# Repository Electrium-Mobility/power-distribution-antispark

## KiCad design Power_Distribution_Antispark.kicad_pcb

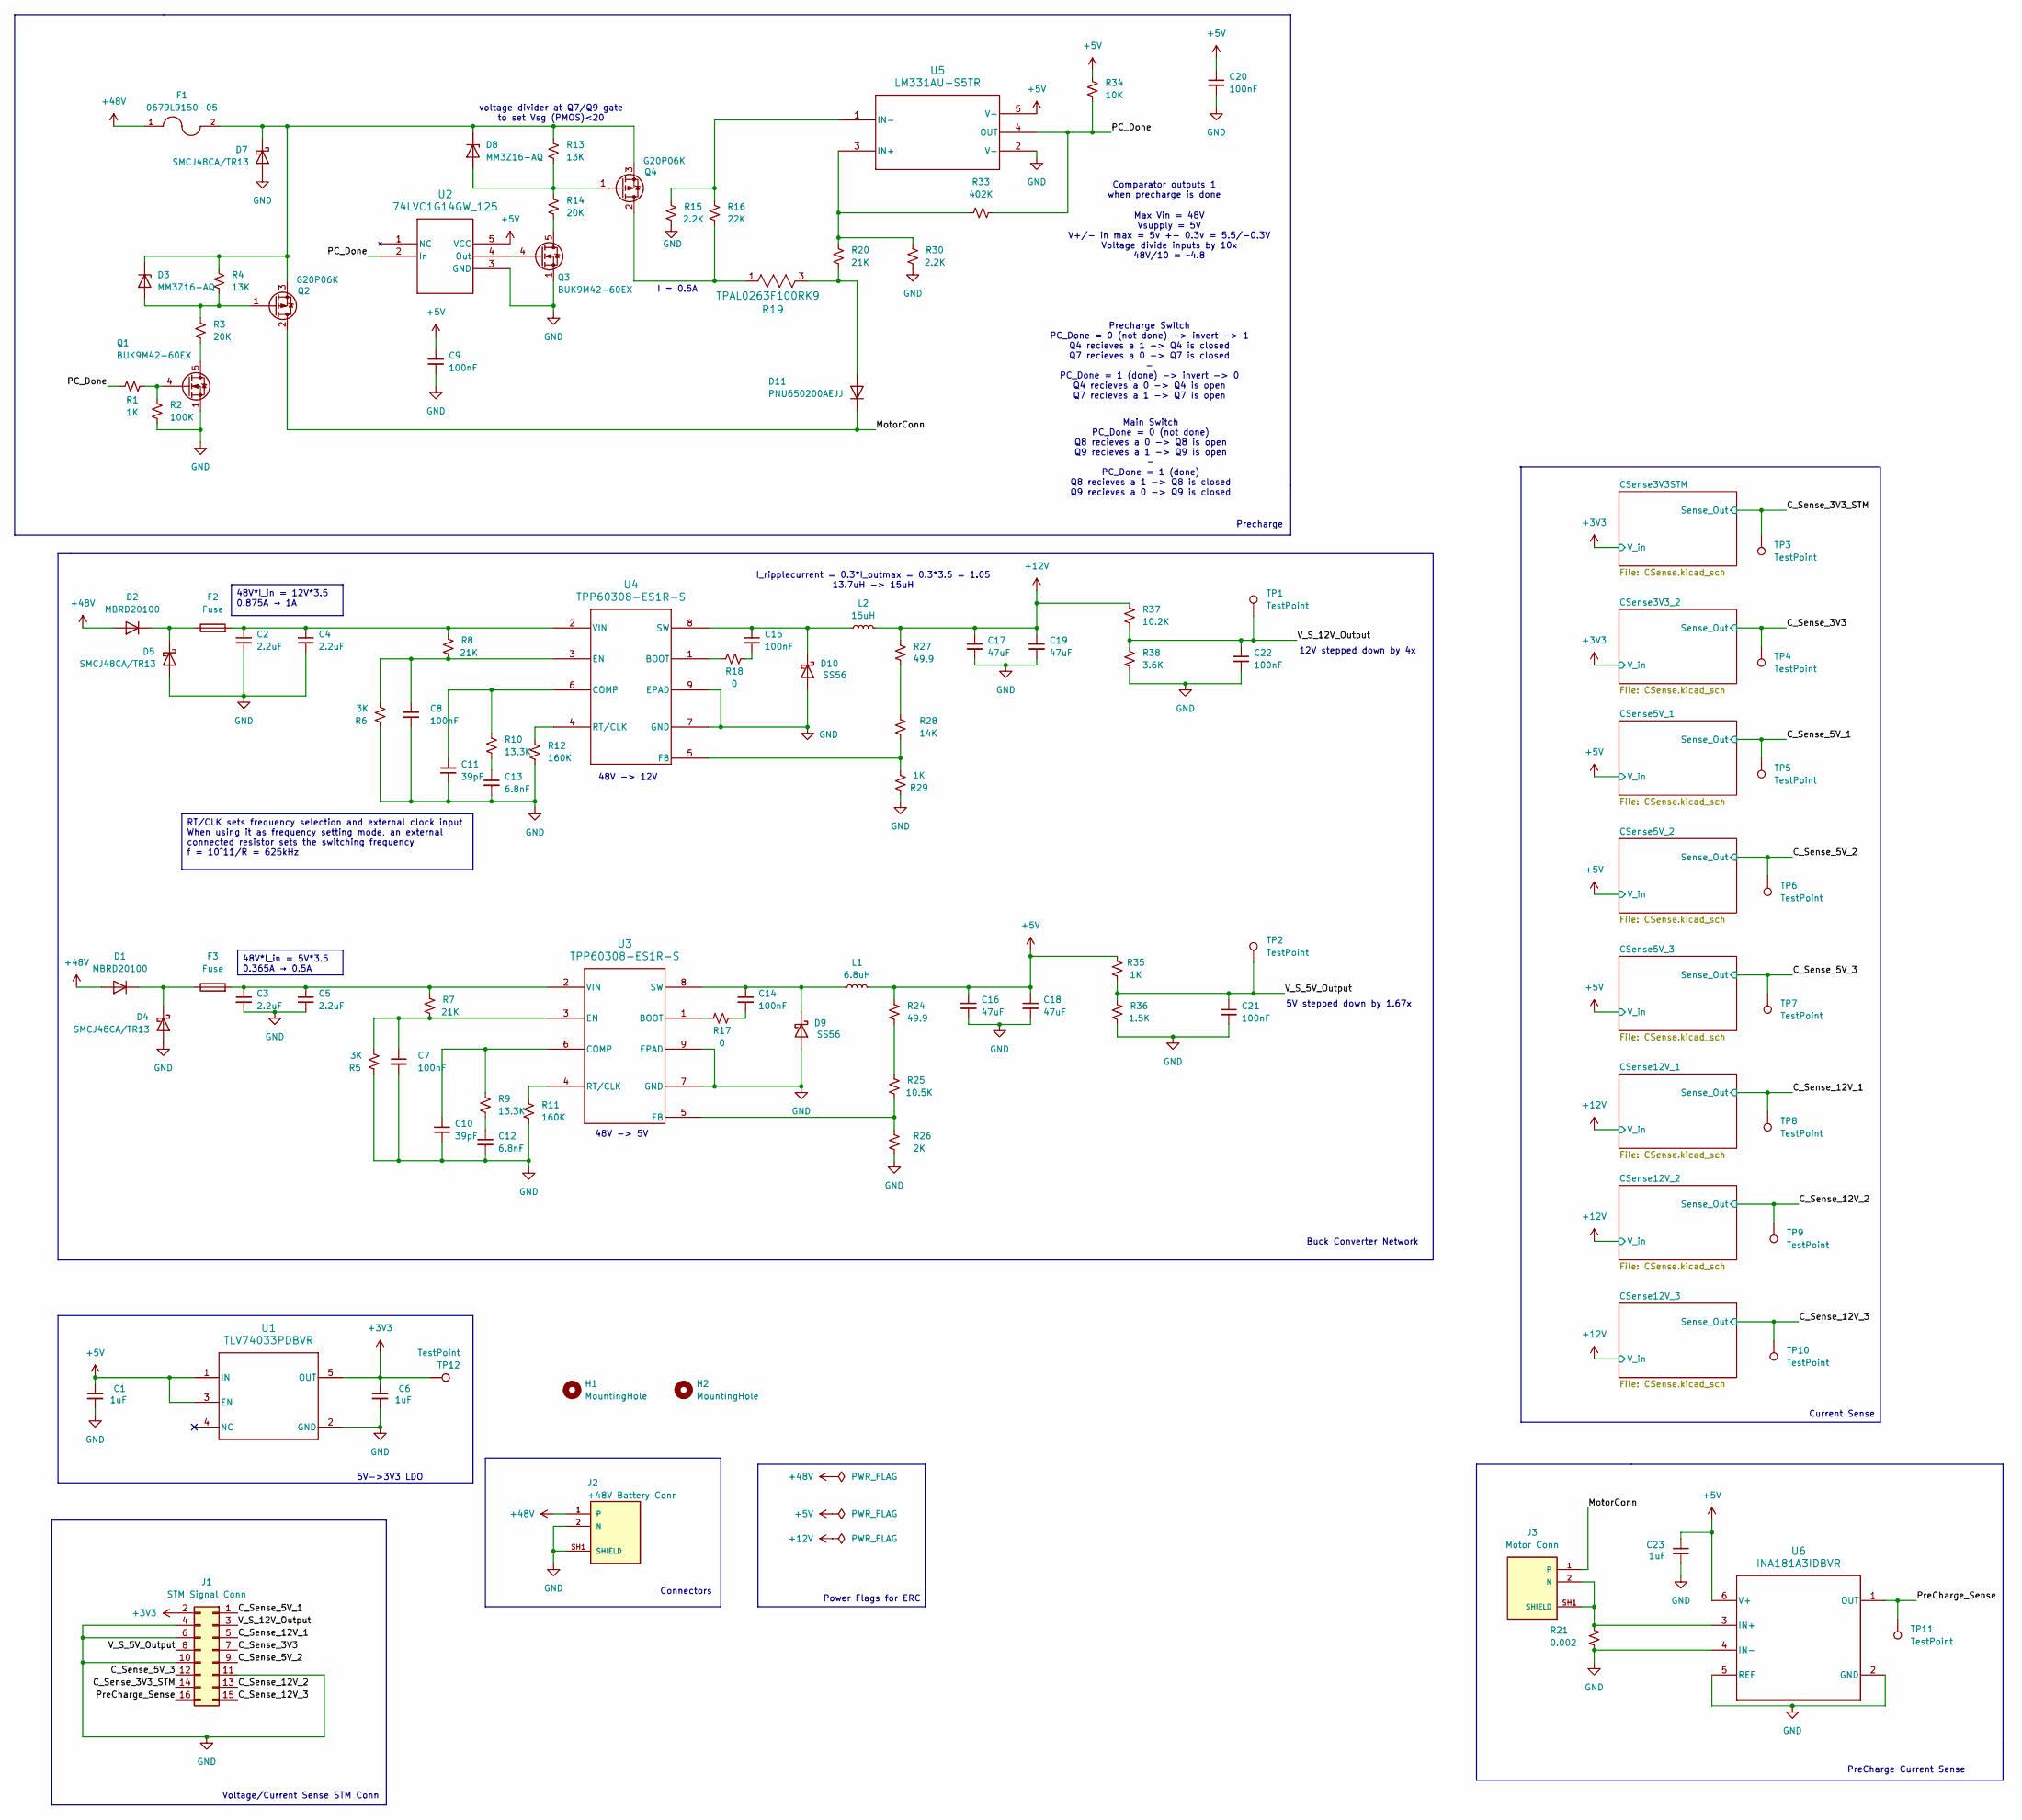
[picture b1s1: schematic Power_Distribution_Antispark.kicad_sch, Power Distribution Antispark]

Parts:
C1, C6, C23: 1uF; C_0603_1608Metric
C2, C3, C4, C5: 2.2uF; C_1206_3216Metric
C7, C8, C9, C14, C15, C20, C21, C22: 100nF; C_0603_1608Metric
C10, C11: 39pF; C_0603_1608Metric
C12, C13: 6.8nF; C_0603_1608Metric
C16, C17, C18, C19: 47uF; C_1206_3216Metric
D1, D2: MBRD20100; TO-252-3_TabPin2
D3, D8: MM3Z16-AQ; D_SOD-323F
D4, D5, D7: SMCJ48CA/TR13; D_SMC
D9, D10: SS56; D_SMA
D11: PNU650200AEJJ; TO-263-3_TabPin2
F1: 0679L9150-05; FUSE_0679L9200-05_BEL; PARTREV 0679H Apr2019
F2, F3: Fuse; Fuse_0603_1608Metric
H1, H2: MountingHole; MountingHole_2.5mm
J1: STM Signal Conn; CONN16_B16B-PHDSS_JST
J2: +48V Battery Conn; AMASS_XT60PW-F; PARTREV 1.2
J3: Motor Conn; AMASS_XT60PW-F; PARTREV 1.2
L1: 6.8uH; IND_MGAH06036R8M-10
L2: 15uH; IND_AMRM00101040_PUL-AMRM00101040150MA1
Q1, Q3: BUK9M42-60EX; LFPAK33
Q2, Q4: G20P06K; TO-252-3_TabPin2
R1, R29, R35: 1K; R_0603_1608Metric
R2: 100K; R_0603_1608Metric
R3, R14: 20K; R_0603_1608Metric
R4, R13: 13K; R_0603_1608Metric
R5, R6: 3K; R_0603_1608Metric
R7, R8, R20: 21K; R_0603_1608Metric
R9, R10: 13.3K; R_0603_1608Metric
R11, R12: 160K; R_0603_1608Metric
R15, R30: 2.2K; R_0603_1608Metric
R16: 22K; R_0603_1608Metric
R17, R18: 0; R_0603_1608Metric
R19: TPAL0263F100RK9; TO-263-2
R21: 0.002; R_0805_2012Metric
R24, R27: 49.9; R_0603_1608Metric
R25: 10.5K; R_0603_1608Metric
R26: 2K; R_0603_1608Metric
R28: 14K; R_0603_1608Metric
R33: 402K; R_0603_1608Metric
R34: 10K; R_0603_1608Metric
R36: 1.5K; R_0603_1608Metric
R37: 10.2K; R_0603_1608Metric
R38: 3.6K; R_0603_1608Metric
TP1, TP2, TP3, TP4, TP5, TP6, TP7, TP8, TP9, TP10, TP11, TP12: TestPoint; TestPoint_Pad_D1.0mm
U1: TLV74033PDBVR
U2: 74LVC1G14GW_125; SOT353_NEX
U3, U4: TPP60308-ES1R-S; ES1ESOP-8-F_TPK
U5: LM331AU-S5TR; S5TSOT23-5-A_TPK
U6: INA181A3IDBVR

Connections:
+3V3: C6.1, J1.2, TP12.1, U1.5 (OUT); also elsewhere on the board
+5V: C1.1, C9.1, C16.1, C18.1, C20.1, C23.1, L1.2, R24.1, R34.1, R35.2, U1.1 (IN), U1.3 (EN), U2.5 (VCC), U5.5 (V+), U6.6 (V+); also elsewhere on the board
+12V: C17.1, C19.1, L2.2, R27.1, R37.1; also elsewhere on the board
+48V: D1.2 (A), D2.2 (A), F1.1, J2.1
/C_Sense_3V3: J1.7, TP4.1; also elsewhere on the board
/C_Sense_3V3_STM: J1.14, TP3.1; also elsewhere on the board
/C_Sense_5V_1: J1.1, TP5.1; also elsewhere on the board
/C_Sense_5V_2: J1.9, TP6.1; also elsewhere on the board
/C_Sense_5V_3: J1.12, TP7.1; also elsewhere on the board
/C_Sense_12V_1: J1.5, TP8.1; also elsewhere on the board
/C_Sense_12V_2: J1.13, TP9.1; also elsewhere on the board
/C_Sense_12V_3: J1.15, TP10.1; also elsewhere on the board
/MotorConn: D11.1 (K), J3.1, Q2.2 (D)
/PC_Done: R1.1, R33.2, R34.2, U2.2 (In), U5.4 (OUT)
/PreCharge_Sense: J1.16, TP11.1, U6.1 (OUT)
/V_S_5V_Output: C21.1, J1.8, R35.1, R36.2, TP2.1
/V_S_12V_Output: C22.1, J1.3, R37.2, R38.1, TP1.1
GND: C1.2, C2.2, C3.2, C4.2, C5.2, C6.2, C7.2, C8.2, C9.2, C10.2, C11.2, C12.2, C13.2, C16.2, C17.2, C18.2, C19.2, C20.2, C21.2, C22.2, C23.2, D4.2 (A), D5.2 (A), D7.2 (A), D9.2 (A), D10.2 (A), J1.4, J1.6, J1.10, J1.11, J2.2 (N), J2.SH1 (SHIELD), J2.SH2 (SHIELD), Q1.1 (S), Q1.2 (S), Q1.3 (S), Q3.1 (S), Q3.2 (S), Q3.3 (S), R2.1, R5.2, R6.2, R11.2, R12.2, R15.1, R21.2, R26.2, R29.1, R30.1, R36.1, R38.2, U1.2 (GND), U2.3 (GND), U3.7 (GND), U3.9 (EPAD), U4.7 (GND), U4.9 (EPAD), U5.2 (V-), U6.2 (GND), U6.4 (IN-), U6.5 (REF); also elsewhere on the board
unnamed: C12.1, R9.2
unnamed: C13.1, R10.2
unnamed: C14.2, R17.2
unnamed: C15.2, R18.2
unnamed: D1.1 (K), D4.1 (K), F3.1
unnamed: D2.1 (K), D5.1 (K), F2.1
unnamed: D3.2 (A), Q2.1 (G), R3.2, R4.2
unnamed: D3.1 (K), D7.1 (K), D8.1 (K), F1.2, Q2.3 (S), Q4.3 (S), R4.1, R13.1
unnamed: D8.2 (A), Q4.1 (G), R13.2, R14.2
unnamed: C14.1, D9.1 (K), L1.1, U3.8 (SW)
unnamed: C15.1, D10.1 (K), L2.1, U4.8 (SW)
unnamed: D11.2 (A), R19.3, R20.1
unnamed: J3.2 (N), J3.SH1 (SHIELD), J3.SH2 (SHIELD), R21.1, U6.3 (IN+)
unnamed: Q1.5 (D), R3.1
unnamed: Q1.4 (G), R1.2, R2.2
unnamed: Q3.5 (D), R14.1
unnamed: Q3.4 (G), U2.4 (Out)
unnamed: Q4.2 (D), R16.1, R19.1
unnamed: R24.2, R25.2
unnamed: R27.2, R28.1
unnamed: R17.1, U3.1 (BOOT)
unnamed: C10.1, R9.1, U3.6 (COMP)
unnamed: C7.1, R5.1, R7.1, U3.3 (EN)
unnamed: R25.1, R26.1, U3.5 (FB)
unnamed: R11.1, U3.4 (RT/CLK)
unnamed: C3.1, C5.1, F3.2, R7.2, U3.2 (VIN)
unnamed: R18.1, U4.1 (BOOT)
unnamed: C11.1, R10.1, U4.6 (COMP)
unnamed: C8.1, R6.1, R8.1, U4.3 (EN)
unnamed: R28.2, R29.2, U4.5 (FB)
unnamed: R12.1, U4.4 (RT/CLK)
unnamed: C2.1, C4.1, F2.2, R8.2, U4.2 (VIN)
unnamed: R20.2, R30.2, R33.1, U5.3 (IN+)
unnamed: R15.2, R16.2, U5.1 (IN-)

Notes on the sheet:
48V -> 5V
12V stepped down by 4x
Connectors
I_ripplecurrent = 0.3*I_outmax = 0.3*3.5 = 1.05 13.7uH -> 15uH
Comparator outputs 1 when precharge is done
Precharge
Precharge Switch PC_Done = 0 (not done) -> invert -> 1 Q4 recieves a 1 -> Q4 is closed Q7 recieves a 0 -> Q7 is closed - PC_Done = 1 (done) -> invert -> 0 Q4 recieves a 0 -> Q4 is open Q7 recieves a 1 -> Q7 is open
voltage divider at Q7/Q9 gate to set Vsg (PMOS)<20
Buck Converter Network
Power Flags for ERC
Voltage/Current Sense STM Conn
Max Vin = 48V Vsupply = 5V V+/- in max = 5v +- 0.3v = 5.5/-0.3V Voltage divide inputs by 10x 48V/10 = ~4.8
48V -> 12V
Current Sense
Main Switch PC_Done = 0 (not done) Q8 recieves a 0 -> Q8 is open Q9 recieves a 1 -> Q9 is open - PC_Done = 1 (done) Q8 recieves a 1 -> Q8 is closed Q9 recieves a 0 -> Q9 is closed
I = 0.5A
5V stepped down by 1.67x
PreCharge Current Sense
5V->3V3 LDO
RT/CLK sets frequency selection and external clock input When using it as frequency setting mode, an external connected resistor sets the switching frequency f = 10^11/R = 625kHz
48V*I_in = 12V*3.5 0.875A → 1A
48V*I_in = 5V*3.5 0.365A → 0.5A

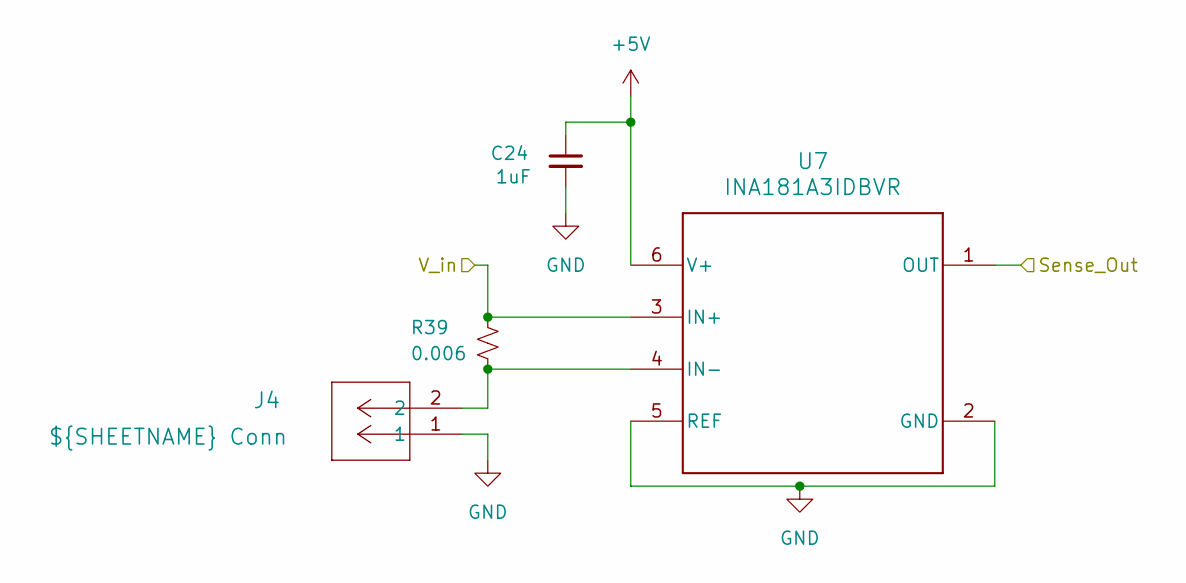
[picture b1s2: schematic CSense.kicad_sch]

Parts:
C24: 1uF; C_0603_1608Metric
J4: ${SHEETNAME} Conn; CONN_B2B-ZR_02P_JST
R39: 0.006; R_0805_2012Metric
U7: INA181A3IDBVR

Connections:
+3V3: R39.1, U7.3 (IN+); also elsewhere on the board
+5V: C24.1, U7.6 (V+); also elsewhere on the board
/C_Sense_3V3_STM: U7.1 (OUT); also elsewhere on the board
GND: C24.2, J4.1, U7.2 (GND), U7.5 (REF); also elsewhere on the board
unnamed: J4.2, R39.2, U7.4 (IN-)

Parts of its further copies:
C25, C26, C27, C28, C29, C30, C31: 1uF; C_0603_1608Metric
R40, R41, R42, R43, R44, R45, R46: 0.006; R_0805_2012Metric
U8, U9, U10, U11, U12, U13, U14: INA181A3IDBVR

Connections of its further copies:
+3V3: R40.1, U8.3 (IN+); also elsewhere on the board
+5V: C25.1, C26.1, C27.1, C28.1, C29.1, C30.1, C31.1, R41.1, R42.1, R43.1, U8.6 (V+), U9.3 (IN+), U9.6 (V+), U10.3 (IN+), U10.6 (V+), U11.3 (IN+), U11.6 (V+), U12.6 (V+), U13.6 (V+), U14.6 (V+); also elsewhere on the board
+12V: R44.1, R45.1, R46.1, U12.3 (IN+), U13.3 (IN+), U14.3 (IN+); also elsewhere on the board
/C_Sense_3V3: U8.1 (OUT); also elsewhere on the board
/C_Sense_5V_1: U9.1 (OUT); also elsewhere on the board
/C_Sense_5V_2: U10.1 (OUT); also elsewhere on the board
/C_Sense_5V_3: U11.1 (OUT); also elsewhere on the board
/C_Sense_12V_1: U12.1 (OUT); also elsewhere on the board
/C_Sense_12V_2: U13.1 (OUT); also elsewhere on the board
/C_Sense_12V_3: U14.1 (OUT); also elsewhere on the board
GND: C25.2, C26.2, C27.2, C28.2, C29.2, C30.2, C31.2, U8.2 (GND), U8.5 (REF), U9.2 (GND), U9.5 (REF), U10.2 (GND), U10.5 (REF), U11.2 (GND), U11.5 (REF), U12.2 (GND), U12.5 (REF), U13.2 (GND), U13.5 (REF), U14.2 (GND), U14.5 (REF); also elsewhere on the board
unnamed 53: R40.2, U8.4 (IN-); also elsewhere on the board
unnamed 54: R41.2, U9.4 (IN-); also elsewhere on the board
unnamed 55: R42.2, U10.4 (IN-); also elsewhere on the board
unnamed 56: R43.2, U11.4 (IN-); also elsewhere on the board
unnamed 57: R44.2, U12.4 (IN-); also elsewhere on the board
unnamed 58: R45.2, U13.4 (IN-); also elsewhere on the board
unnamed 59: R46.2, U14.4 (IN-); also elsewhere on the board

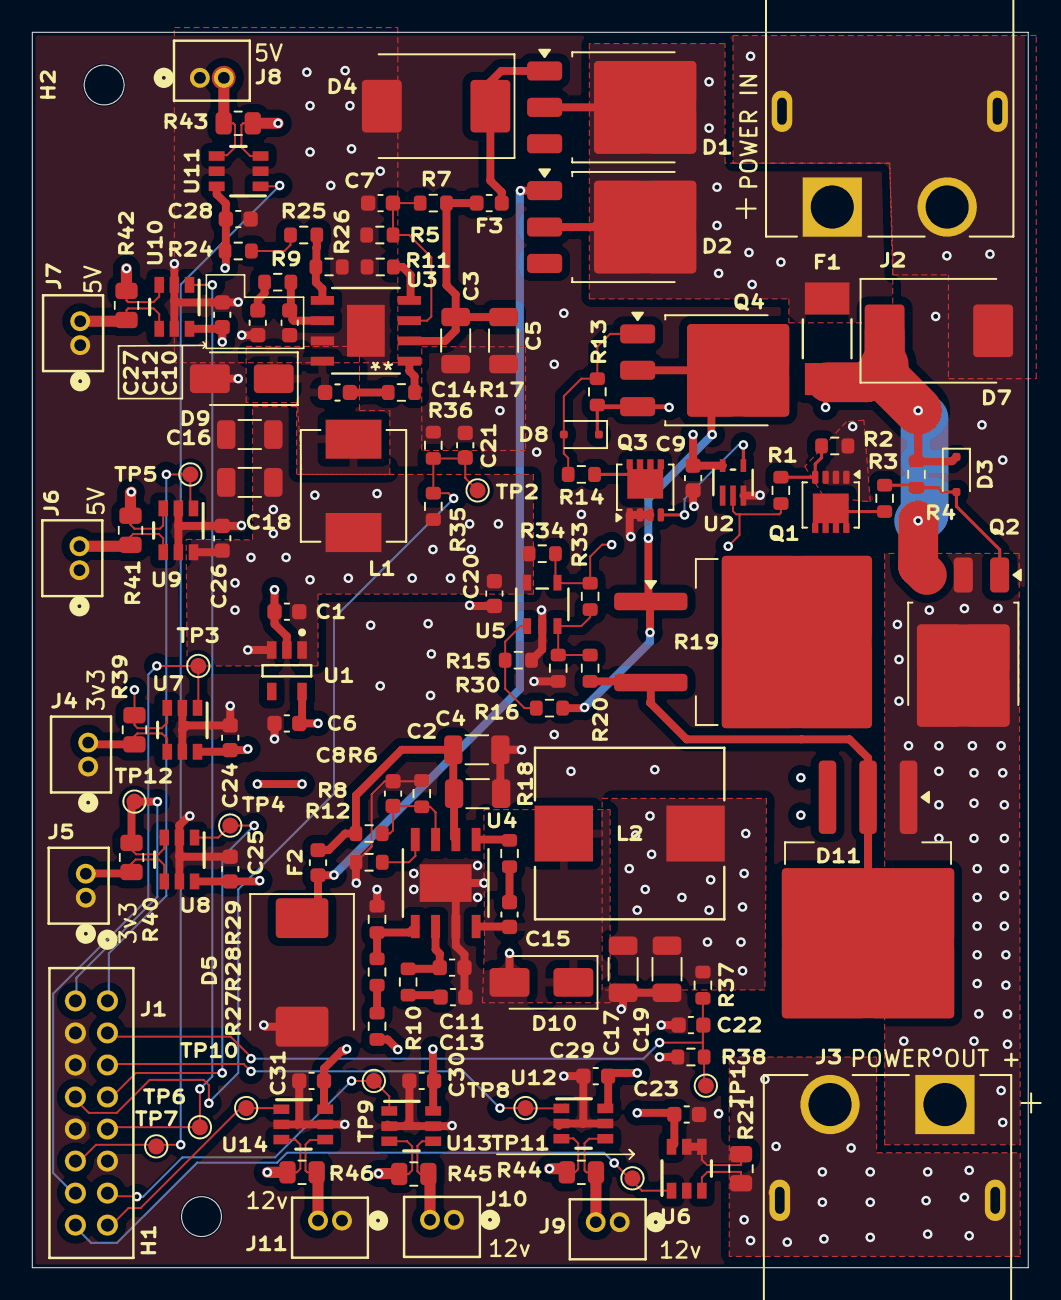
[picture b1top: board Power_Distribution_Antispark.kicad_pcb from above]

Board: 4 copper layers, 62.4 x 77.4 mm, 131 parts (0 on the bottom side), 60 nets.

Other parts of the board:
J5: CSense3V3_2 Conn; CONN_B2B-ZR_02P_JST
J6: CSense5V_1 Conn; CONN_B2B-ZR_02P_JST
J7: CSense5V_2 Conn; CONN_B2B-ZR_02P_JST
J8: CSense5V_3 Conn; CONN_B2B-ZR_02P_JST
J9: CSense12V_1 Conn; CONN_B2B-ZR_02P_JST
J10: CSense12V_2 Conn; CONN_B2B-ZR_02P_JST
J11: CSense12V_3 Conn; CONN_B2B-ZR_02P_JST

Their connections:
GND: J5.1, J6.1, J7.1, J8.1, J9.1, J10.1, J11.1; also elsewhere on the board
unnamed 53: J5.2; also elsewhere on the board
unnamed 54: J6.2; also elsewhere on the board
unnamed 55: J7.2; also elsewhere on the board
unnamed 56: J8.2; also elsewhere on the board
unnamed 57: J9.2; also elsewhere on the board
unnamed 58: J10.2; also elsewhere on the board
unnamed 59: J11.2; also elsewhere on the board

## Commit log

2026-05-26 schematic
2026-05-27 schematic without gate driver
2026-05-27 schematic without resistor cap ind
2026-05-27 schematic without inductor
2026-05-28 schematic for review
2026-05-28 schematic fixed precharge logic
    still need to spec inverter
2026-05-28 updated connectors and inverter
2026-05-28 updated connectors
2026-05-31 schematic update
2026-05-31 changed ldo to buck
2026-05-31 added pull up resistor for comparator
2026-06-01 final schematic
2026-06-09 damir review
2026-06-10 tweaked comparator resistor values
2026-06-10 tweaked comparator values and shunt
2026-06-10 custom library
2026-06-10 minor component datasheet fix + layout started
2026-06-11 component layout
2026-06-11 layout changes
2026-06-11 redid layout components
2026-06-11 different layout
2026-06-12 layout2
2026-06-12 most traces
2026-06-12 all traces
2026-06-12 updated traces
2026-06-14 layout review + fixed polygon pour shapes
2026-06-14 layout update
2026-06-16 layout post review
2026-06-18 fixed silkscreens
2026-06-19 fixed connectors
2026-06-19 fixed leo layout review
2026-06-21 final layout + logo added
2026-06-22 added date and rev number
2026-06-29 changed main pmos
